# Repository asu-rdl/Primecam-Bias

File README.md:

# Primecam-Bias

See [https://asu-rdl.github.io/Primecam-Bias/](https://asu-rdl.github.io/Primecam-Bias/)

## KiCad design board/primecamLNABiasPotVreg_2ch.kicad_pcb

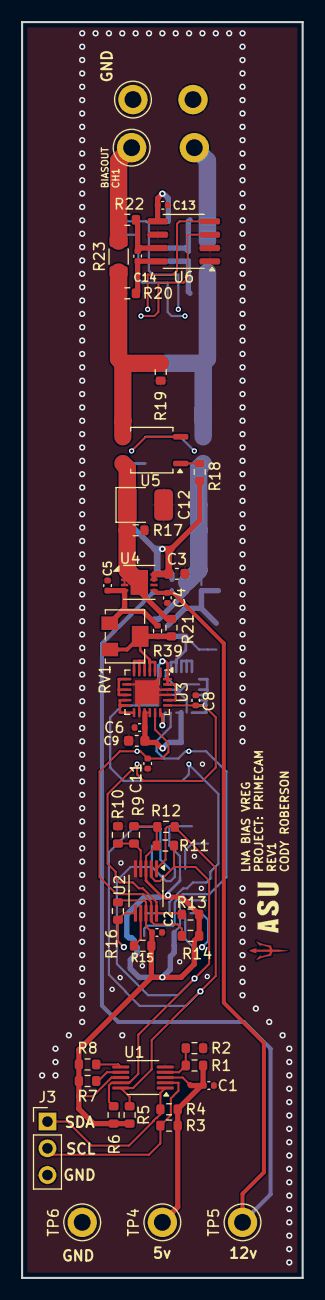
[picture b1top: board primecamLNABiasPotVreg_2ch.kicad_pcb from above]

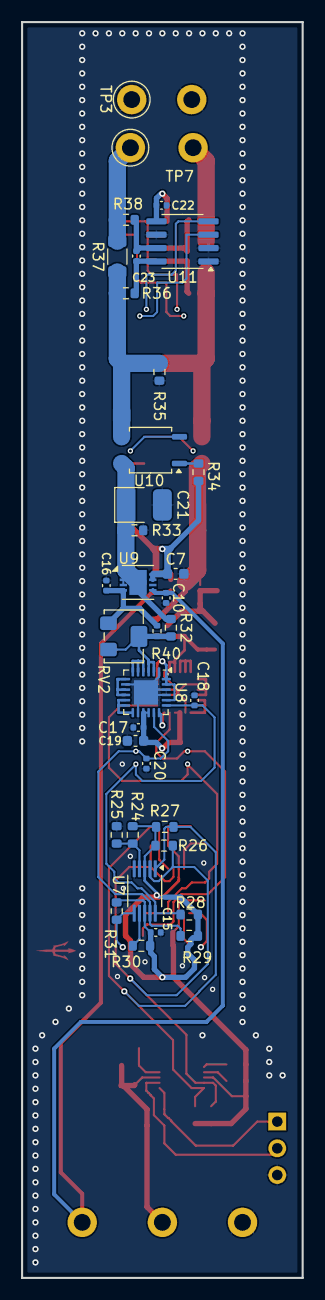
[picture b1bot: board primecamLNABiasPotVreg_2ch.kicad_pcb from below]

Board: 4 copper layers, 26.7 x 119.4 mm, 84 parts (35 on the bottom side), 42 nets.

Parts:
C1, C2, C15: 10nF; C_0402_1005Metric
C3, C7, C9, C19: 10u; C_0603_1608Metric
C4, C6, C10, C13, C14, C17, C22, C23: 0.1u; C_0402_1005Metric
C5, C16: 4.7u; C_0402_1005Metric
C8, C11, C18, C20: 10p; C_0402_1005Metric
C12, C21: 10u; Cap_b_1411
J3: Conn_01x03; PinHeader_1x03_P2.54mm_Vertical
R1: 2800; R_0603_1608Metric
R2: 137; R_0603_1608Metric
R3, R4, R7, R8, R11, R12, R15, R16, R26, R27, R30, R31: 10K; R_0603_1608Metric
R5, R6, R13, R14, R28, R29: 5.1K; R_0603_1608Metric
R9, R24: 1150; R_0603_1608Metric
R10, R25: 2050; R_0603_1608Metric
R17, R33: 200; R_0603_1608Metric
R18, R34: 3k65; R_0603_1608Metric
R19, R35: 1k; R_0603_1608Metric
R20, R21, R22, R32, R36, R38: 10; R_0603_1608Metric
R23, R37: 1; R_1206_3216Metric
R39, R40: 0; R_0402_1005Metric
RV1, RV2: POT_40k; Potentiometer_Bourns_3224W_Vertical
TP1, TP2, TP3, TP4, TP5, TP6, TP7: TestPoint; TestPoint_Keystone_5005-5009_Compact
U1, U2, U7: LTC4302-1; MSOP-10_3x3mm_P0.5mm
U3, U8: AD5144_100k; LFCSP-24-1EP_4x4mm_P0.5mm_EP2.3x2.3mm
U4, U9: LT3080xDD; DFN-8-1EP_3x3mm_P0.5mm_EP1.66x2.38mm
U5, U10: AQY212G3HS; SOP-4_3.8x4.1mm_P2.54mm
U6, U11: INA219AxD; SOIC-8_3.9x4.9mm_P1.27mm

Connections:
5V: C1.2, C2.2, C3.1, C6.2, C7.1, C9.1, C13.1, C15.2, C17.2, C19.1, C22.1, R1.1, R3.1, R4.1, R5.1, R6.1, R7.1, R8.1, R9.1, R11.1, R12.1, R13.1, R14.1, R15.1, R16.1, R18.2, R24.1, R26.1, R27.1, R28.1, R29.1, R30.1, R31.1, R34.2, TP4.1, U1.3 (CONN), U1.8 (Vcc), U2.3 (CONN), U2.8 (Vcc), U3.15 (VDD), U3.16 (V_LOGIC), U3.18 (DIS), U3.20 (~WP), U3.23 (~LRDAC), U3.24 (~RESET), U4.7 (IN), U4.8 (IN), U6.5 (VS), U7.3 (CONN), U7.8 (Vcc), U8.15 (VDD), U8.16 (V_LOGIC), U8.18 (DIS), U8.20 (~WP), U8.23 (~LRDAC), U8.24 (~RESET), U9.7 (IN), U9.8 (IN), U11.5 (VS)
12V: C4.1, C10.1, TP5.1, U4.5 (V_{CONTROL}), U9.5 (V_{CONTROL})
/BIAS_OUT_CH1: R22.2, R23.2, TP2.1
/BIAS_OUT_CH2: R37.2, R38.2, TP7.1
/BiasCircuit1/GPIO1: R31.2, U7.6 (GPIO1), U10.2
/BiasCircuit1/SCL2: C20.2, R29.2, U7.9 (SCLOUT), U8.17 (SCL), U11.4 (SCL)
/BiasCircuit1/SDA2: C18.2, R28.2, U7.10 (SDAOUT), U8.19 (SDA), U11.3 (SDA)
/BiasCircuit/GPIO1: R16.2, U2.6 (GPIO1), U5.2
/BiasCircuit/SCL1: C11.2, R14.2, U2.9 (SCLOUT), U3.17 (SCL), U6.4 (SCL)
/BiasCircuit/SDA1: C8.2, R13.2, U2.10 (SDAOUT), U3.19 (SDA), U6.3 (SDA)
/SCL_BiasCircuit: R6.2, R11.2, R26.2, U1.9 (SCLOUT), U2.2 (SCLIN), U7.2 (SCLIN)
/SDA_BiasCircuit: R5.2, R12.2, R27.2, U1.10 (SDAOUT), U2.1 (SDAIN), U7.1 (SDAIN)
GND: C1.1, C2.1, C3.2, C4.2, C5.2, C6.1, C7.2, C8.1, C9.2, C10.2, C11.1, C12.2, C13.2, C15.1, C16.2, C17.1, C18.1, C19.2, C20.1, C21.2, C22.2, J3.3, R2.2, R10.2, R17.2, R19.2, R25.2, R33.2, R35.2, TP1.1, TP3.1, TP6.1, U1.5 (GND), U2.5 (GND), U3.1 (GND), U3.8 (VSS), U3.14 (B4), U3.21 (ADDR1), U3.22 (ADDR0), U3.25 (PAD), U6.1 (A1), U6.2 (A0), U6.6 (GND), U7.5 (GND), U8.1 (GND), U8.8 (VSS), U8.14 (B4), U8.21 (ADDR1), U8.22 (ADDR0), U8.25 (PAD), U11.1 (A1), U11.2 (A0), U11.6 (GND)
unnamed: C12.1, R17.1, R21.1, U4.1 (OUT), U4.2 (OUT), U4.3 (OUT), U4.9 (OUT), U5.4
unnamed: C21.1, R32.1, R33.1, U9.1 (OUT), U9.2 (OUT), U9.3 (OUT), U9.9 (OUT), U10.4
unnamed: R18.1, U5.1
unnamed: R19.1, R20.2, R23.1, U5.3
unnamed: R34.1, U10.1
unnamed: R35.1, R36.2, R37.1, U10.3
unnamed: R1.2, R2.1, U1.4 (ADD)
unnamed: R8.2, U1.6 (GPIO1)
unnamed: R7.2, U1.7 (GPIO2)
unnamed: R9.2, R10.1, U2.4 (ADD)
unnamed: R15.2, U2.7 (GPIO2)
unnamed: R21.2, R39.2, RV1.2, RV1.3, U3.2 (A1), U3.3 (W1)
unnamed: U3.7 (B3), U3.9 (A2), U3.10 (W2)
unnamed: U3.4 (B1), U3.5 (A3), U3.6 (W3)
unnamed: U3.11 (B2), U3.12 (A4), U3.13 (W4)
unnamed: C5.1, R39.1, RV1.1, U4.4 (SET)
unnamed: C14.2, R20.1, U6.8 (IN+)
unnamed: C14.1, R22.1, U6.7 (IN-)
unnamed: R24.2, R25.1, U7.4 (ADD)
unnamed: R30.2, U7.7 (GPIO2)
unnamed: R32.2, R40.2, RV2.2, RV2.3, U8.2 (A1), U8.3 (W1)
unnamed: U8.7 (B3), U8.9 (A2), U8.10 (W2)
unnamed: U8.4 (B1), U8.5 (A3), U8.6 (W3)
unnamed: U8.11 (B2), U8.12 (A4), U8.13 (W4)
unnamed: C16.1, R40.1, RV2.1, U9.4 (SET)
unnamed: C23.2, R36.1, U11.8 (IN+)
unnamed: C23.1, R38.1, U11.7 (IN-)
SCL_LTC0: J3.2, R3.2, U1.2 (SCLIN)
SDA_LTC0: J3.1, R4.2, U1.1 (SDAIN)

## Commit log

2025-04-04 Uploaded board
    Revision 1, Layout modified to reflect Top circuit layout onto back copper. Potentially ready for implementation of full VME card design.
2025-04-04 Added Arduino code for prototype testbench
    Meant to be used with an Arduino Nano Every
2025-04-04 added docs
2025-04-04 Init orphaned branch for docs
2025-04-04 updated docs, experiment
2025-04-04 update docs
2025-04-09 added build via docker
    Created a cargo package. Configured for both x86_64 and aarch64 for the
    raspberry pi. Added ingredients for cross compiling via docker image.
2025-04-09 updated makefile
2025-04-09 updated makefile
    There was a better way to handle the container instead of dropping
    the user into an interactive shell that they would then need to exit out
    of. This may lead to confusion
2025-04-09 tested CLI lib clap
2025-04-18 updated docs on main. Do Not publish.
2025-04-18 removed rust project, favoring python impl
2025-04-19 init python project, add cli
    Added a CLI skeleton for board testing. Updated documentation
2025-04-19 Updated docs to match eb787da
2025-04-21 impl some LowLevel board functions
2025-04-21 added ina219 addresses
2025-05-07 added ina219 implementation
    fix addresses, ina219 datatypes
    Fixed INA219 datatypes. Current sense chip returns two's compliment
    signed values which erroneously treated as uint16 when it should be
    int16. This resulted in negative shunt voltages such as -0.1 mV being
    reported as 635.35mV which is not possbile.
    Wiper addresses were not currect. They are now.
2025-05-14 put some skelington on them daemons
    Added some meat to them bones
    yes
2025-05-27 Adjust hardware.py
    Changed TI8474 to TI8475 and needed to accomodate that. We have 16 bits
    to control instead of 8 as before. Added test loads to the cards.
2025-05-27 plan for mutexclusion
2025-05-29 created testscript
2025-05-29 mod testscript to make it editable install
2025-05-30 fixed bug
2025-06-02 added logging
    Happy with redis setup
    idk dawg
2025-06-03 added features usefull for testing
    updated docs
    added formatted reply class
    working on command parsing
2025-06-04 began writing unit tests
2025-06-06 Future me, practice historical revisionism here
2025-06-06 Fixed commanding and pass unit testing for getstatus
2025-06-06 implemented the rest of the unimplemented commands
2025-06-06 commitycommit
2025-06-06 updateboard, added seekcurrenttest
2025-06-10 Moved card, channel verification to valid_command()
2025-06-11 bugfix, summary updates
2025-06-11 added systemd service def and tested
    It works. It actually works. wooo
2025-06-11 build image and deployed to pi
2025-06-11 added save/load function
2025-06-11 more testing
2025-06-11 bug fix
2025-06-12 added update script
2025-06-12 oops
2025-06-12 silent failure on no redis server present. Oops
2025-06-12 fixed updater
2025-06-18 added more to the docs
2025-06-18 updated docs from main
2025-06-18 updated docs some more.
2025-06-18 added hardware docs
2025-06-18 added more docs
